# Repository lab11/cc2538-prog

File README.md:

cc2538-prog
===========

Programmers for the CC2538.

So far includes one board that connects the SmartRF06 board to a tagconnect
cable to program an arm based board.

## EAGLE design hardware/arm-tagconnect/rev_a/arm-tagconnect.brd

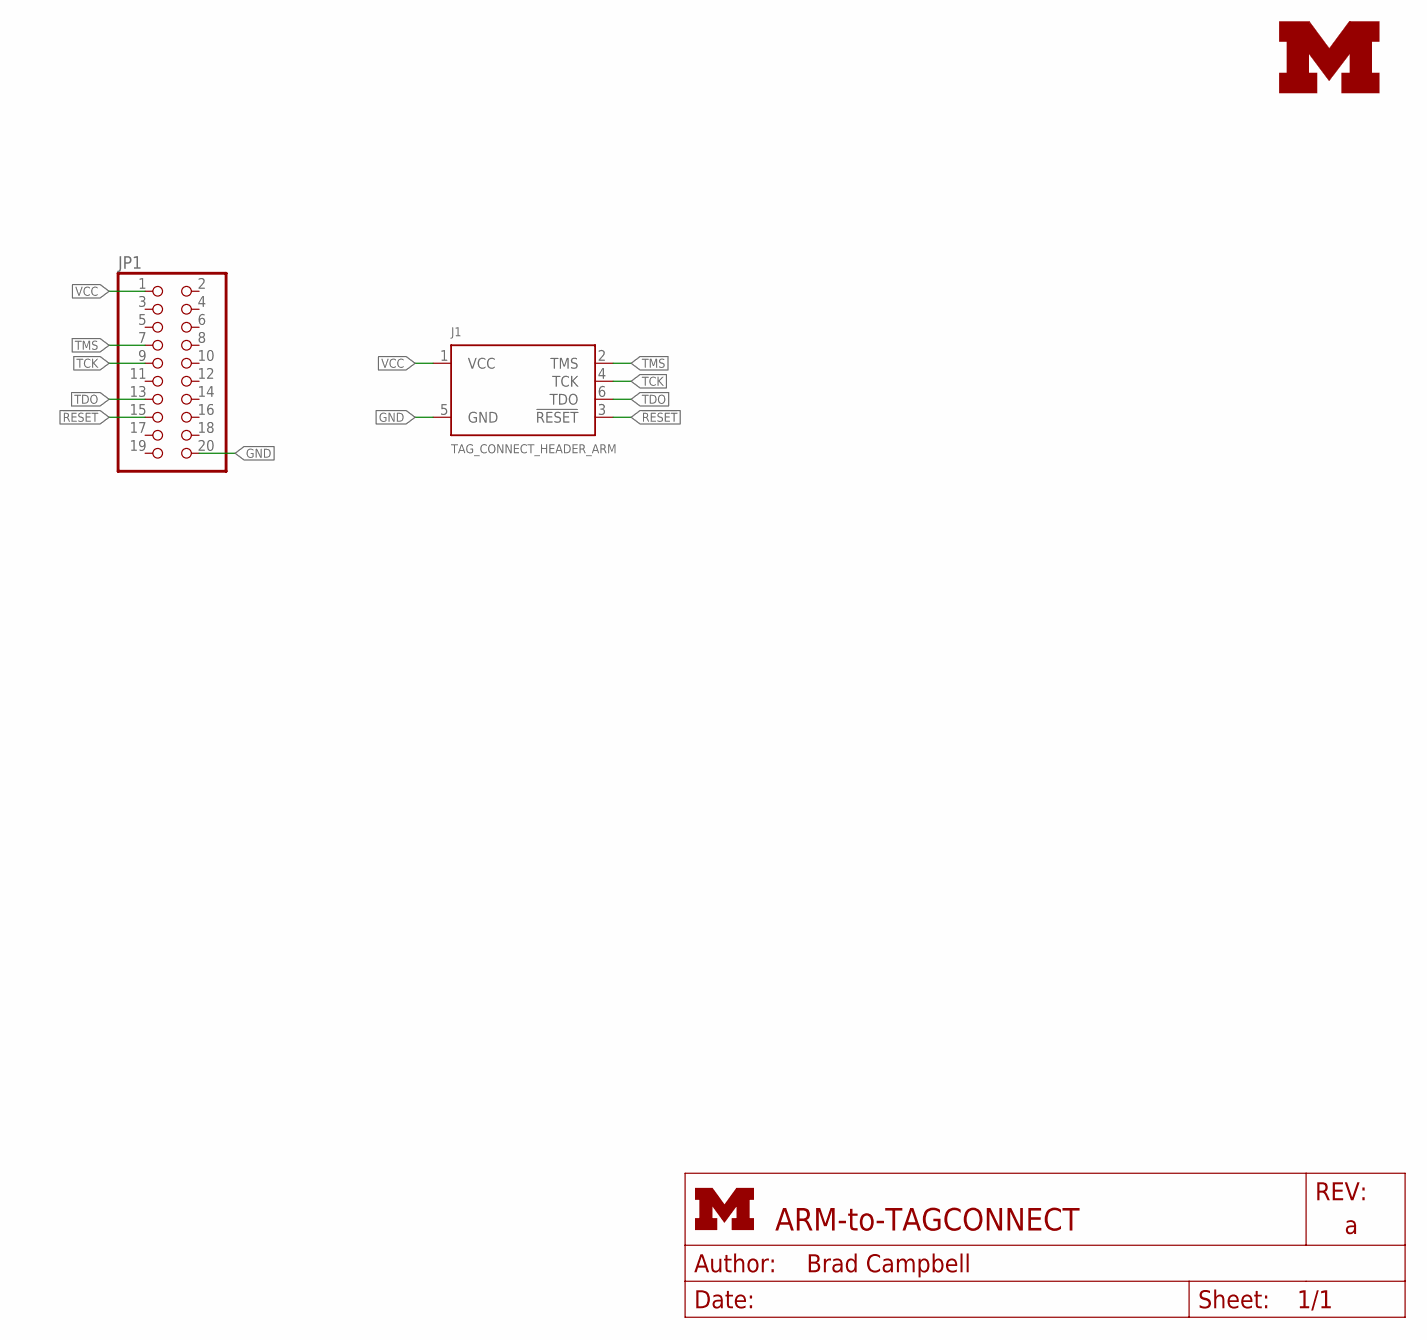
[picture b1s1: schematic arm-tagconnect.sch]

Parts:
J1: TAG_CONNECT_HEADER_ARM; 2X3_MALE_SHROUDED_0.100
JP1: PINHD-2X10; 2X10
LOGO1: UMICH_SOLID_SMALL; UMICH_SOLID_75MIL

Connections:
!RESET: J1.3 (!RESET), JP1.15
GND: J1.5 (GND), JP1.20
TCK: J1.4 (TCK), JP1.9
TDO: J1.6 (TDO), JP1.13
TMS: J1.2 (TMS), JP1.7
VCC: J1.1 (VCC), JP1.1

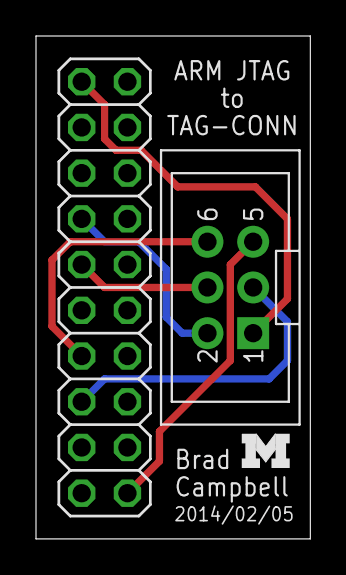
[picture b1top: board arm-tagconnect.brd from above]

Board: 2 copper layers, 15.2 x 27.9 mm, 3 parts (0 on the bottom side), 6 nets.

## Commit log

2014-02-11 arm-tag connect adapter
2014-02-11 gitignore
